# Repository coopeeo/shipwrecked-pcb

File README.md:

# shipwrecked-pcb
Shipwrecked PCB Badges

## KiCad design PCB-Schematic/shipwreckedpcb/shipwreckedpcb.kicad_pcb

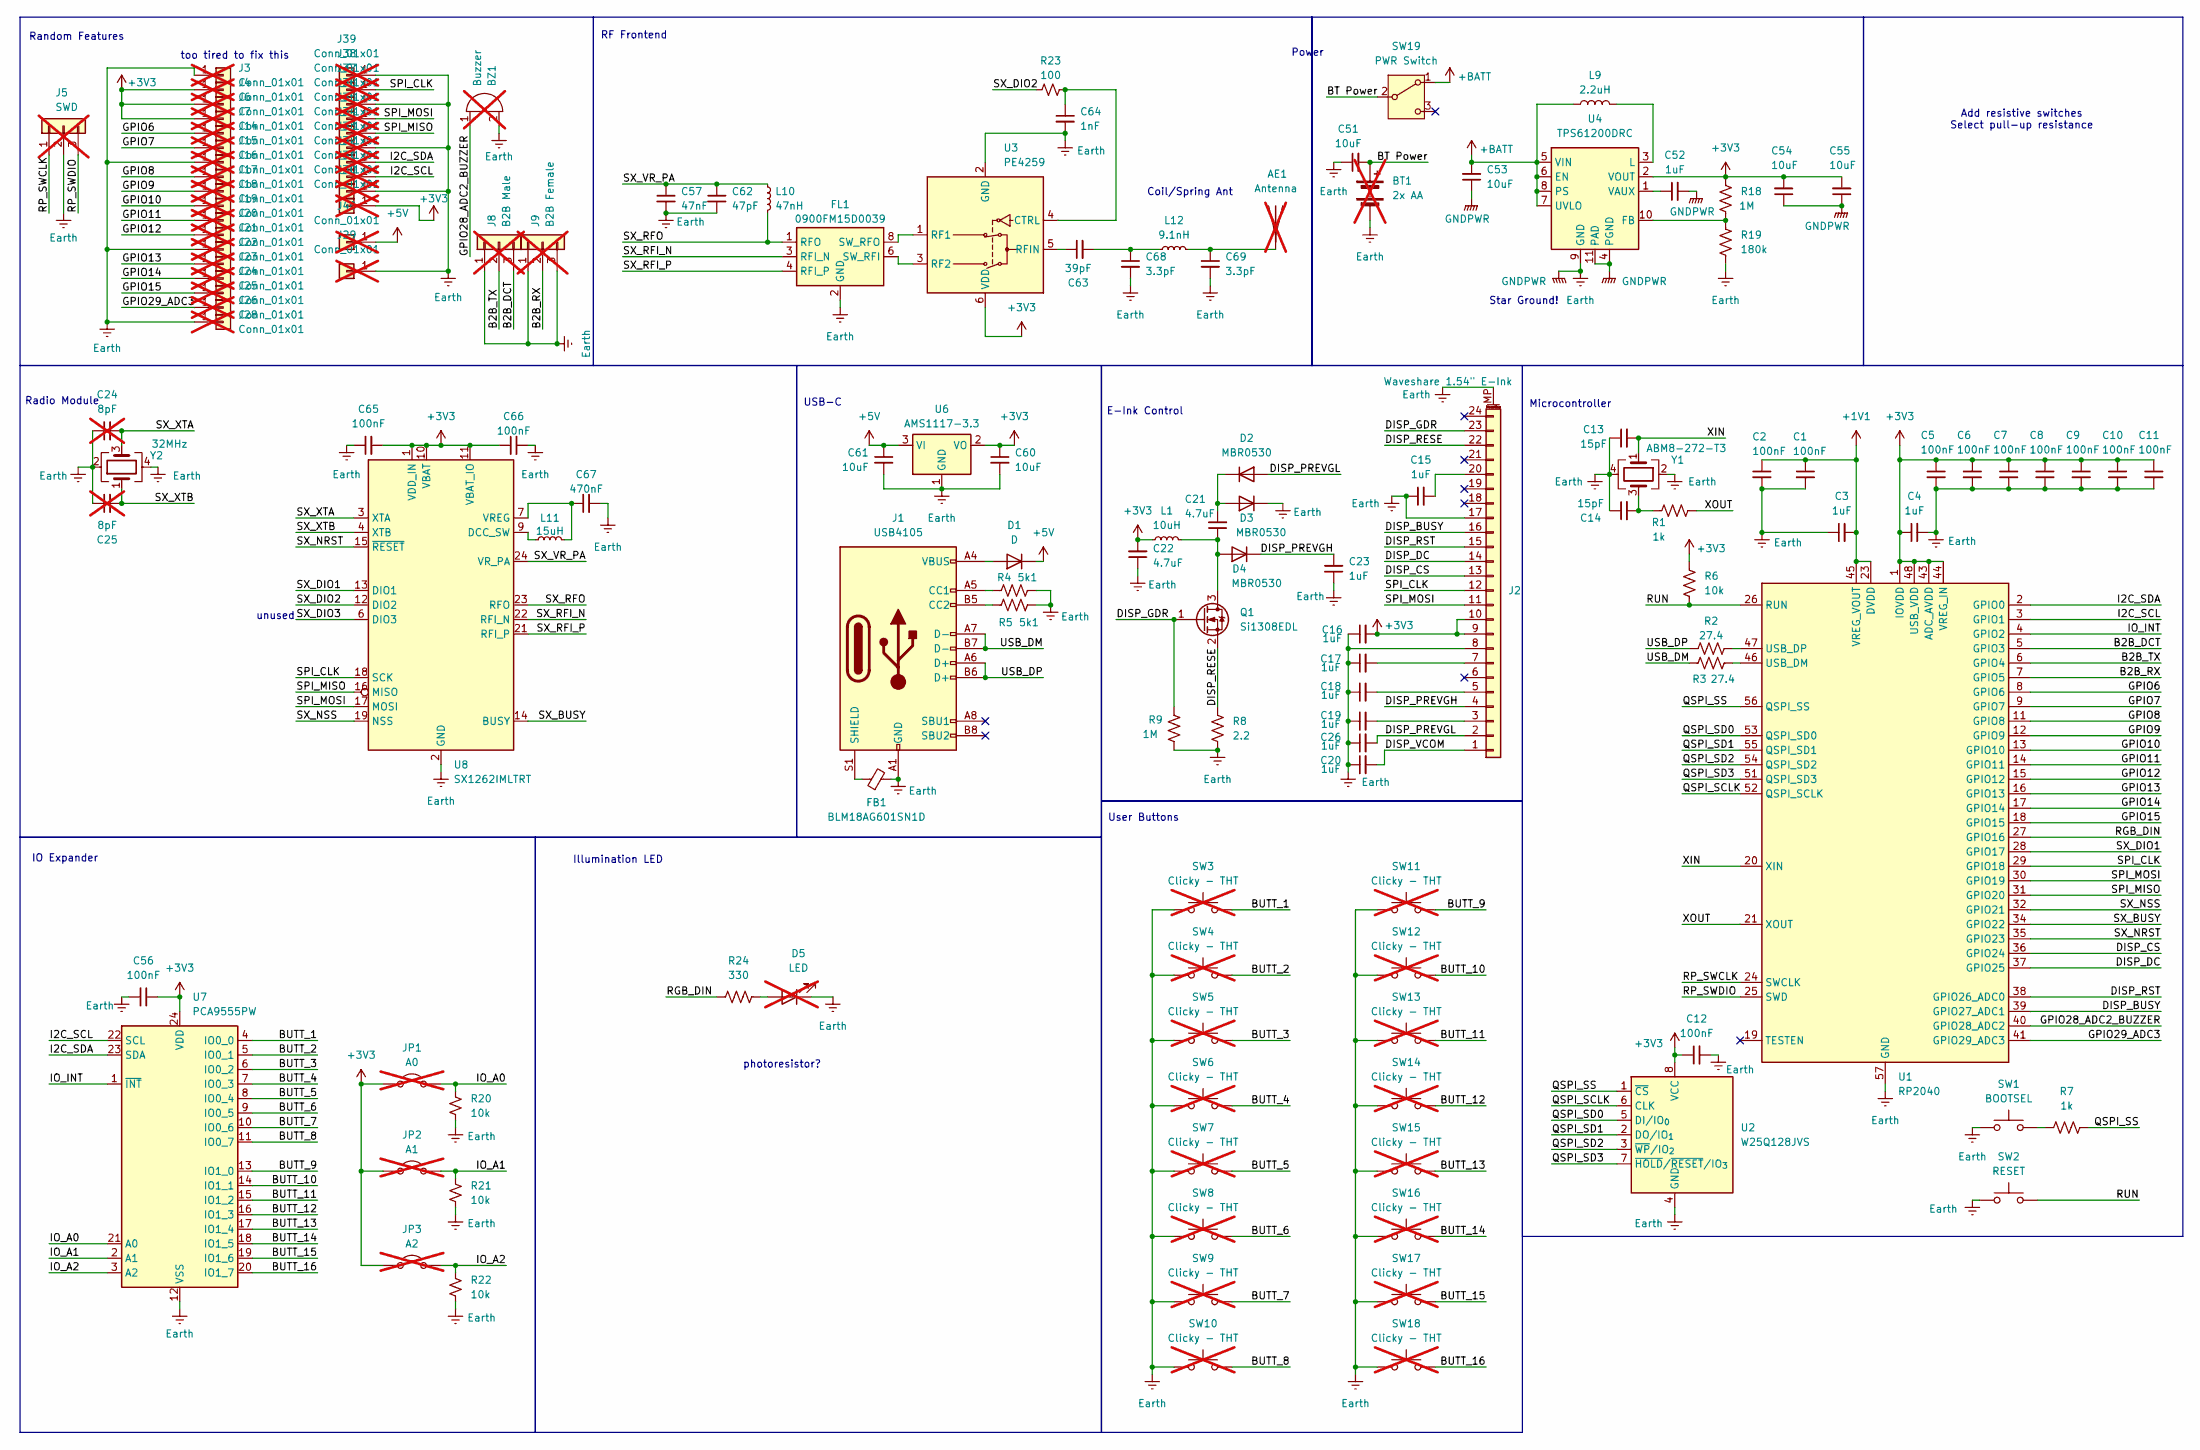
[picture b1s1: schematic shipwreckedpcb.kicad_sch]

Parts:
AE1: Antenna; PinSocket_1x01_P2.54mm_Vertical; not fitted
BT1: 2x AA; BatteryHolder_Keystone_2462_2xAA; not fitted
BZ1: Buzzer; Buzzer_D14mm_H7mm_P10mm; not fitted
C1, C2, C5, C6, C7, C8, C9, C10, C11, C12, C56, C65, C66: 100nF; C_0603_1608Metric; MPN CC0603KRX7R9BB104; LCSC Part C14663
C3, C4, C15, C16, C17, C18, C19, C20, C23, C26, C52: 1uF; C_0603_1608Metric; MPN CL10A105KB8NNNC; LCSC Part C15849
C13, C14: 15pF; C_0603_1608Metric; MPN CC0603JRNPO9BN150; LCSC Part C1644
C21, C22: 4.7uF; C_0603_1608Metric; MPN CL10A475KA8NQNC; LCSC Part C69335
C24, C25: 8pF; C_0603_1608Metric; MPN CC0603CRNPO9BN8R0; not fitted
C51, C53, C54, C55, C60, C61: 10uF; C_0603_1608Metric; MPN CL10A106KP8NNNC; LCSC Part C96446
C57: 47nF; C_0603_1608Metric; MPN CC0603KRX7R9BB473; LCSC Part C1622
C62: 47pF; C_0603_1608Metric; MPN CC0603JRNPO9BN470; LCSC Part C1671
C63: 39pF; C_0603_1608Metric; MPN CC0603JRNPO9BN101; LCSC Part C1666
C64: 1nF; C_0603_1608Metric; MPN CC0603KRX7R9BB102; LCSC Part C1588
C67: 470nF; C_0603_1608Metric; MPN CL10B474KA8NNNC; LCSC Part C1623
C68, C69: 3.3pF; C_0603_1608Metric; MPN 0603CG3R3C500NT; LCSC Part C1660
D1: D; D_SOD-123F; MPN 1N4001; LCSC Part C2892326
D2, D3, D4: MBR0530; D_SOD-123; MPN MBR0530T1G; LCSC Part C77336
D5: LED; LED_D5.0mm; MPN DY-324SVRC-H23-P-A4(FH); not fitted
FB1: BLM18AG601SN1D; R_0603_1608Metric; MPN BLM18AG601SN1D; LCSC Part C19330
FL1: 0900FM15D0039; Balun_Johanson_0900FM15K0039; MPN 0900FM15K0039E; LCSC Part consigned
J1: USB4105; USB_C_Receptacle_GCT_USB4105-xx-A_16P_TopMnt_Horizontal; MPN USB4105-GF-A; LCSC Part C3020560
J2: Waveshare 1.54" E-Ink; TE_2-1734839-4_1x24-1MP_P0.5mm_Horizontal; MPN 05B20U24P; LCSC Part C5362165
J3, J4, J6, J7, J14, J15, J16, J17, J18, J19, J20, J21, J22, J23, J24, J25, J26, J28, J29, J30, J31, J32, J33, J34, J35, J36, J37, J38, J39, J40: Conn_01x01; SolderWirePad_1x01_SMD_1x2mm; not fitted
J5: SWD; PinSocket_1x03_P2.54mm_Vertical; not fitted
J8: B2B Male; PinHeader_1x03_P2.54mm_Horizontal; not fitted
J9: B2B Female; PinSocket_1x03_P2.54mm_Horizontal; not fitted
JP1: A0; SolderJumper-2_P1.3mm_Open_RoundedPad1.0x1.5mm; not fitted
JP2: A1; SolderJumper-2_P1.3mm_Open_RoundedPad1.0x1.5mm; not fitted
JP3: A2; SolderJumper-2_P1.3mm_Open_RoundedPad1.0x1.5mm; not fitted
L1: 10uH; L_APV_ANR4018; MPN FNR4018S100MT; LCSC Part C167808
L9: 2.2uH; L_Taiyo-Yuden_NR-30xx; MPN NR3015T2R2M; LCSC Part C6364793
L10: 47nH; L_0603_1608Metric; MPN LS0603-47NJ-N; LCSC Part C285885
L11: 15uH; L_0805_2012Metric; MPN MLZ2012M150WT000; LCSC Part C383402
L12: 9.1nH; L_0603_1608Metric; MPN LS0603-47NJ-N; LCSC Part C334262
Q1: Si1308EDL; SOT-323_SC-70; MPN SI1308EDL; LCSC Part C7603347
R1, R7: 1k; R_0603_1608Metric; MPN RC0603FR-071KL; LCSC Part C21190
R2, R3: 27.4; R_0603_1608Metric; MPN FRC0603F27R4TS; LCSC Part C22926
R4, R5: 5k1; R_0603_1608Metric; MPN FRC0603F5101TS; LCSC Part C23186
R6, R20, R21, R22: 10k; R_0603_1608Metric; MPN RC0603FR-0710KL; LCSC Part C25804
R8: 2.2; R_0603_1608Metric; MPN CRCW06033R00FKEA; LCSC Part C22939
R9, R18: 1M; R_0603_1608Metric; MPN RC0603FR-071ML; LCSC Part C22935
R19: 180k; R_0603_1608Metric; MPN FRC0603F1803TS; LCSC Part C22827
R23: 100; R_0603_1608Metric; MPN RC0603FR-07100RL; LCSC Part C22775
R24: 330; R_0603_1608Metric; MPN RC0603FR-07330RL; LCSC Part C23138
SW1: BOOTSEL; SW_Tactile_SPST_NO_Straight_CK_PTS636Sx25SMTRLFS; MPN TS-1101-C-W; LCSC Part C318938
SW2: RESET; SW_Tactile_SPST_NO_Straight_CK_PTS636Sx25SMTRLFS; MPN TS-1101-C-W; LCSC Part C318938
SW3, SW4, SW5, SW6, SW7, SW8, SW9, SW10, SW11, SW12, SW13, SW14, SW15, SW16, SW17, SW18: Clicky - THT; SW_PUSH_6mm; MPN SH-6X6X4.3H-CJ; not fitted
SW19: PWR Switch; SW_SPDT_PCM12; MPN SK-3296S-01-L1; LCSC Part C319020
U1: RP2040; QFN-56-1EP_7x7mm_P0.4mm_EP3.2x3.2mm; MPN RP2040; LCSC Part C2040
U2: W25Q128JVS; SOIC-8_5.3x5.3mm_P1.27mm; MPN W25Q128JVSIQ; LCSC Part C97521
U3: PE4259; SOT-363_SC-70-6; MPN PE4259-63; LCSC Part C470892
U4: TPS61200DRC; Texas_S-PVSON-N10_ThermalVias; MPN TPS61200DRCR; LCSC Part C140320
U6: AMS1117-3.3; SOT-223-3_TabPin2; MPN AMS1117-3.3V; LCSC Part C18906017
U7: PCA9555PW; TSSOP-24_4.4x7.8mm_P0.65mm; MPN PCA9555PW,118; LCSC Part C128392
U8: SX1262IMLTRT; QFN-24-1EP_4x4mm_P0.5mm_EP2.6x2.6mm; MPN SX1262IMLTRT; LCSC Part C191341
Y1: ABM8-272-T3; Crystal_SMD_Abracon_ABM8G-4Pin_3.2x2.5mm; MPN XL2EL89CMI-111YLC-12M; LCSC Part C9002
Y2: 32MHz; Crystal_SMD_3225-4Pin_3.2x2.5mm; MPN XTM32032000DT00351001; LCSC Part C19723365

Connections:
+1V1: C1.1, C2.1, C3.2, U1.23 (DVDD), U1.45 (VREG_VOUT), U1.50 (DVDD)
+3V3: C4.1, C5.1, C6.1, C7.1, C8.1, C9.1, C10.1, C11.1, C12.1, C16.2, C22.2, C54.2, C55.2, C56.1, C60.1, C65.2, C66.1, J2.9, J2.10, J4.1, J6.1, J7.1, J30.1, JP1.1 (A), JP2.1 (A), JP3.1 (A), L1.1, R6.1, R18.1, U1.1 (IOVDD), U1.10 (IOVDD), U1.22 (IOVDD), U1.33 (IOVDD), U1.42 (IOVDD), U1.43 (ADC_AVDD), U1.44 (VREG_IN), U1.48 (USB_VDD), U1.49 (IOVDD), U2.8 (VCC), U3.6 (VDD), U4.2 (VOUT), U6.2 (VO), U7.24 (VDD), U8.1 (VDD_IN), U8.10 (VBAT), U8.11 (VBAT_IO)
+5V: C61.1, D1.1 (K), J40.1, U6.3 (VI)
+BATT: C53.2, L9.1, SW19.1 (A), U4.5 (VIN), U4.6 (EN), U4.7 (UVLO), U4.8 (PS)
/B2B_DCT: J8.3, U1.5 (GPIO3)
/B2B_RX: J9.2, U1.7 (GPIO5)
/B2B_TX: J8.2, U1.6 (GPIO4)
/BT Power: BT1.1 (+), C51.2, SW19.2 (B)
/BUTT_1: SW3.2, U7.4 (IO0_0)
/BUTT_2: SW4.2, U7.5 (IO0_1)
/BUTT_3: SW5.2, U7.6 (IO0_2)
/BUTT_4: SW6.2, U7.7 (IO0_3)
/BUTT_5: SW7.2, U7.8 (IO0_4)
/BUTT_6: SW8.2, U7.9 (IO0_5)
/BUTT_7: SW9.2, U7.10 (IO0_6)
/BUTT_8: SW10.2, U7.11 (IO0_7)
/BUTT_9: SW11.2, U7.13 (IO1_0)
/BUTT_10: SW12.2, U7.14 (IO1_1)
/BUTT_11: SW13.2, U7.15 (IO1_2)
/BUTT_12: SW14.2, U7.16 (IO1_3)
/BUTT_13: SW15.2, U7.17 (IO1_4)
/BUTT_14: SW16.2, U7.18 (IO1_5)
/BUTT_15: SW17.2, U7.19 (IO1_6)
/BUTT_16: SW18.2, U7.20 (IO1_7)
/DISP_BUSY: J2.16, U1.39 (GPIO27_ADC1)
/DISP_CS: J2.13, U1.36 (GPIO24)
/DISP_DC: J2.14, U1.37 (GPIO25)
/DISP_GDR: J2.23, Q1.1 (G), R9.1
/DISP_PREVGH: C23.2, D4.1 (K), J2.4
/DISP_PREVGL: C26.2, D2.2 (A), J2.2
/DISP_RESE: J2.22, Q1.2 (S), R8.1
/DISP_RST: J2.15, U1.38 (GPIO26_ADC0)
/DISP_VCOM: C20.2, J2.1
/GPIO6: J14.1, U1.8 (GPIO6)
/GPIO7: J15.1, U1.9 (GPIO7)
/GPIO8: J17.1, U1.11 (GPIO8)
/GPIO9: J18.1, U1.12 (GPIO9)
/GPIO10: J19.1, U1.13 (GPIO10)
/GPIO11: J20.1, U1.14 (GPIO11)
/GPIO12: J21.1, U1.15 (GPIO12)
/GPIO13: J23.1, U1.16 (GPIO13)
/GPIO14: J24.1, U1.17 (GPIO14)
/GPIO15: J25.1, U1.18 (GPIO15)
/GPIO28_ADC2_BUZZER: BZ1.1 (+), U1.40 (GPIO28_ADC2)
/GPIO29_ADC3: J26.1, U1.41 (GPIO29_ADC3)
/I2C_SCL: J32.1, U1.3 (GPIO1), U7.22 (SCL)
/I2C_SDA: J33.1, U1.2 (GPIO0), U7.23 (SDA)
/IO_A0: JP1.2 (B), R20.1, U7.21 (A0)
/IO_A1: JP2.2 (B), R21.1, U7.2 (A1)
/IO_A2: JP3.2 (B), R22.1, U7.3 (A2)
/IO_INT: U1.4 (GPIO2), U7.1 (~INT)
/QSPI_SCLK: U1.52 (QSPI_SCLK), U2.6 (CLK)
/QSPI_SD0: U1.53 (QSPI_SD0), U2.5 (DI/IO_{0})
/QSPI_SD1: U1.55 (QSPI_SD1), U2.2 (DO/IO_{1})
/QSPI_SD2: U1.54 (QSPI_SD2), U2.3 (~WP/IO_{2})
/QSPI_SD3: U1.51 (QSPI_SD3), U2.7 (~HOLD/~RESET/IO_{3})
/QSPI_SS: R7.2, U1.56 (QSPI_SS), U2.1 (~CS)
/RGB_DIN: R24.1, U1.27 (GPIO16)
/RP_SWCLK: J5.1, U1.24 (SWCLK)
/RP_SWDIO: J5.3, U1.25 (SWD)
/RUN: R6.2, SW2.2, U1.26 (RUN)
/SPI_CLK: J2.12, J38.1, U1.29 (GPIO18), U8.18 (SCK)
/SPI_MISO: J35.1, U1.31 (GPIO20), U8.16 (MISO)
/SPI_MOSI: J2.11, J36.1, U1.30 (GPIO19), U8.17 (MOSI)
/SX_BUSY: U1.34 (GPIO22), U8.14 (BUSY)
/SX_DIO1: U1.28 (GPIO17), U8.13 (DIO1)
/SX_DIO2: R23.1, U8.12 (DIO2)
/SX_DIO3: U8.6 (DIO3)
/SX_NRST: U1.35 (GPIO23), U8.15 (~RESET)
/SX_NSS: U1.32 (GPIO21), U8.19 (NSS)
/SX_RFI_N: FL1.3 (RFI_N), U8.22 (RFI_N)
/SX_RFI_P: FL1.4 (RFI_P), U8.21 (RFI_P)
/SX_RFO: FL1.1 (RFO), L10.2, U8.23 (RFO)
/SX_VR_PA: C57.1, C62.1, L10.1, U8.24 (VR_PA)
/SX_XTA: C24.2, U8.3 (XTA), Y2.3
/SX_XTB: C25.2, U8.4 (XTB), Y2.1
/USB_DM: J1.A7 (D-), J1.B7 (D-), R3.1
/USB_DP: J1.A6 (D+), J1.B6 (D+), R2.1
/XIN: C13.2, U1.20 (XIN), Y1.1
/XOUT: R1.2, U1.21 (XOUT)
Earth: BT1.2 (-), BZ1.2 (-), C1.2, C2.2, C3.1, C4.2, C5.2, C6.2, C7.2, C8.2, C9.2, C10.2, C11.2, C12.2, C13.1, C14.1, C15.1, C16.1, C17.1, C18.1, C19.1, C20.1, C22.1, C23.1, C24.1, C25.1, C26.1, C51.1, C52.2, C53.1, C54.1, C55.1, C56.2, C57.2, C60.2, C61.2, C62.2, C64.2, C65.1, C66.2, C67.2, C68.2, C69.2, D3.1 (K), D5.1 (K), FB1.2, FL1.2 (GND), FL1.5 (GND), FL1.7 (GND), FL1.9 (GND), FL1.10 (GND), J1.A1 (GND), J1.A12 (GND), J1.B1 (GND), J1.B12 (GND), J2.8, J2.17, J2.MP (MountPin), J3.1, J5.2, J8.1, J9.1, J9.3, J16.1, J22.1, J28.1, J29.1, J31.1, J34.1, J37.1, J39.1, R4.2, R5.2, R8.2, R9.2, R19.2, R20.2, R21.2, R22.2, SW1.1, SW2.1, SW3.1, SW4.1, SW5.1, SW6.1, SW7.1, SW8.1, SW9.1, SW10.1, SW11.1, SW12.1, SW13.1, SW14.1, SW15.1, SW16.1, SW17.1, SW18.1, U1.57 (GND), U2.4 (GND), U3.2 (GND), U4.4 (PGND), U4.9 (GND), U4.11 (PAD), U6.1 (GND), U7.12 (VSS), U8.2 (GND), U8.5 (GND), U8.8 (GND), U8.20 (GND), U8.25 (GND), Y1.2, Y1.4, Y2.2, Y2.4
unnamed: AE1.1 (A), C69.1, L12.2
unnamed: C14.2, R1.1, Y1.3
unnamed: C63.2, C68.1, L12.1
unnamed: D1.2 (A), J1.A4 (VBUS), J1.A9 (VBUS), J1.B4 (VBUS), J1.B9 (VBUS)
unnamed: C21.2, D2.1 (K), D3.2 (A)
unnamed: C21.1, D4.2 (A), L1.2, Q1.3 (D)
unnamed: D5.2 (A), R24.2
unnamed: FL1.6 (SW_RFI), U3.3 (RF2)
unnamed: FL1.8 (SW_RFO), U3.1 (RF1)
unnamed: J1.A5 (CC1), R4.1
unnamed: J1.B5 (CC2), R5.1
unnamed: FB1.1, J1.S1 (SHIELD)
unnamed: C19.2, J2.3
unnamed: C18.2, J2.5
unnamed: C17.2, J2.7
unnamed: C15.2, J2.20
unnamed: R7.1, SW1.2
unnamed: R3.2, U1.46 (USB_DM)
unnamed: R2.2, U1.47 (USB_DP)
unnamed: C64.1, R23.2, U3.4 (CTRL)
unnamed: C63.1, U3.5 (RFIN)
unnamed: R18.2, R19.1, U4.10 (FB)
unnamed: L9.2, U4.3 (L)
unnamed: C52.1, U4.1 (VAUX)
unnamed: L11.1, U8.9 (DCC_SW)
unnamed: C67.1, L11.2, U8.7 (VREG)

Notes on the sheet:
IO Expander
photoresistor?
Illumination LED
Power
Add resistive switches Select pull-up resistance
Microcontroller
E-Ink Control
unused
User Buttons
Star Ground!
too tired to fix this
Coil/Spring Ant
Random Features
RF Frontend
USB-C
Radio Module

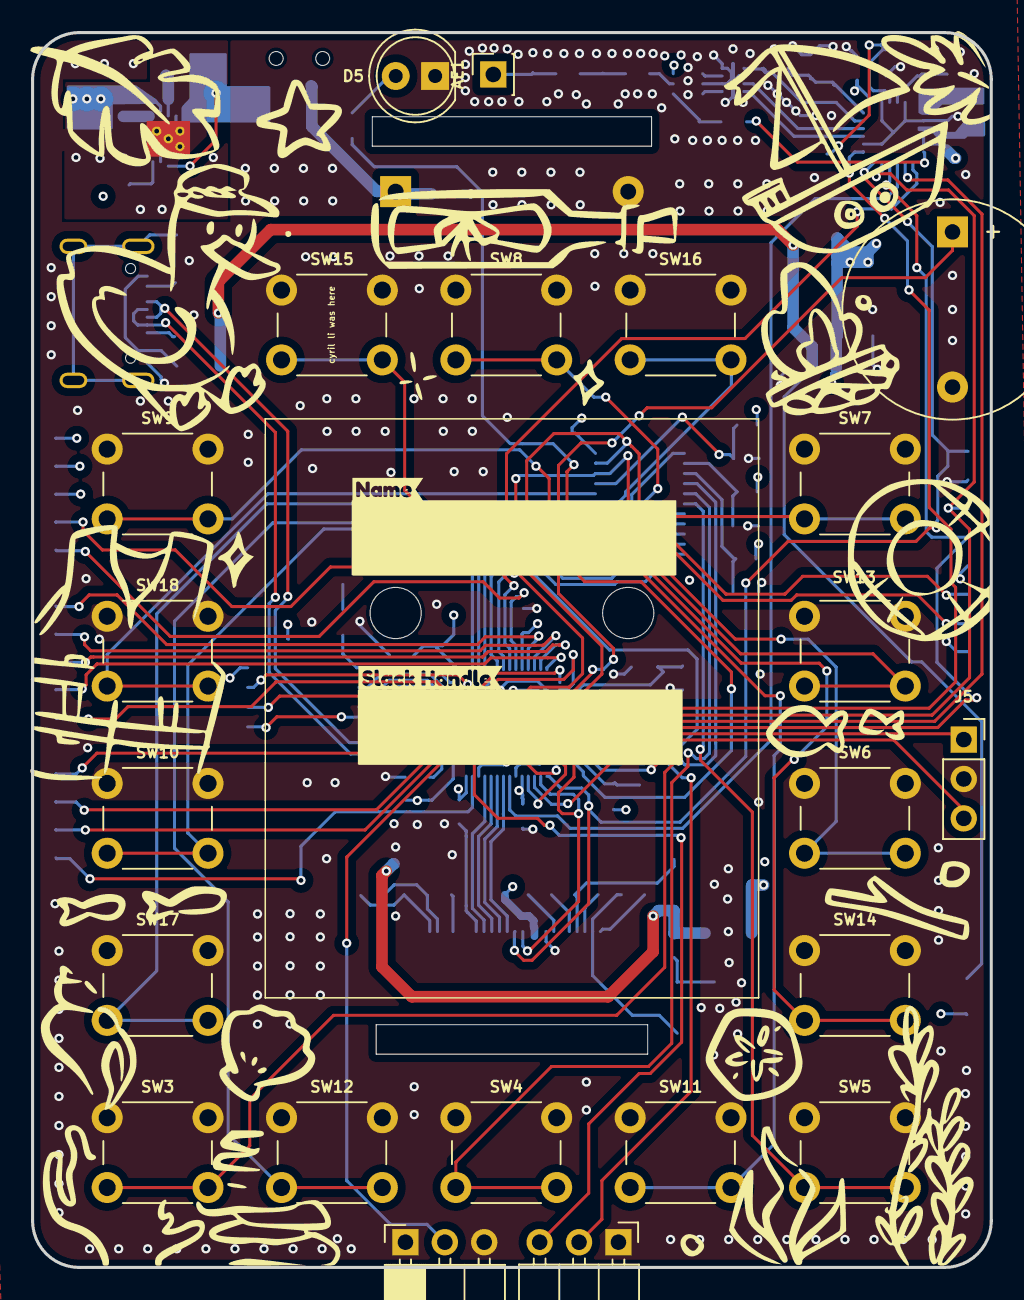
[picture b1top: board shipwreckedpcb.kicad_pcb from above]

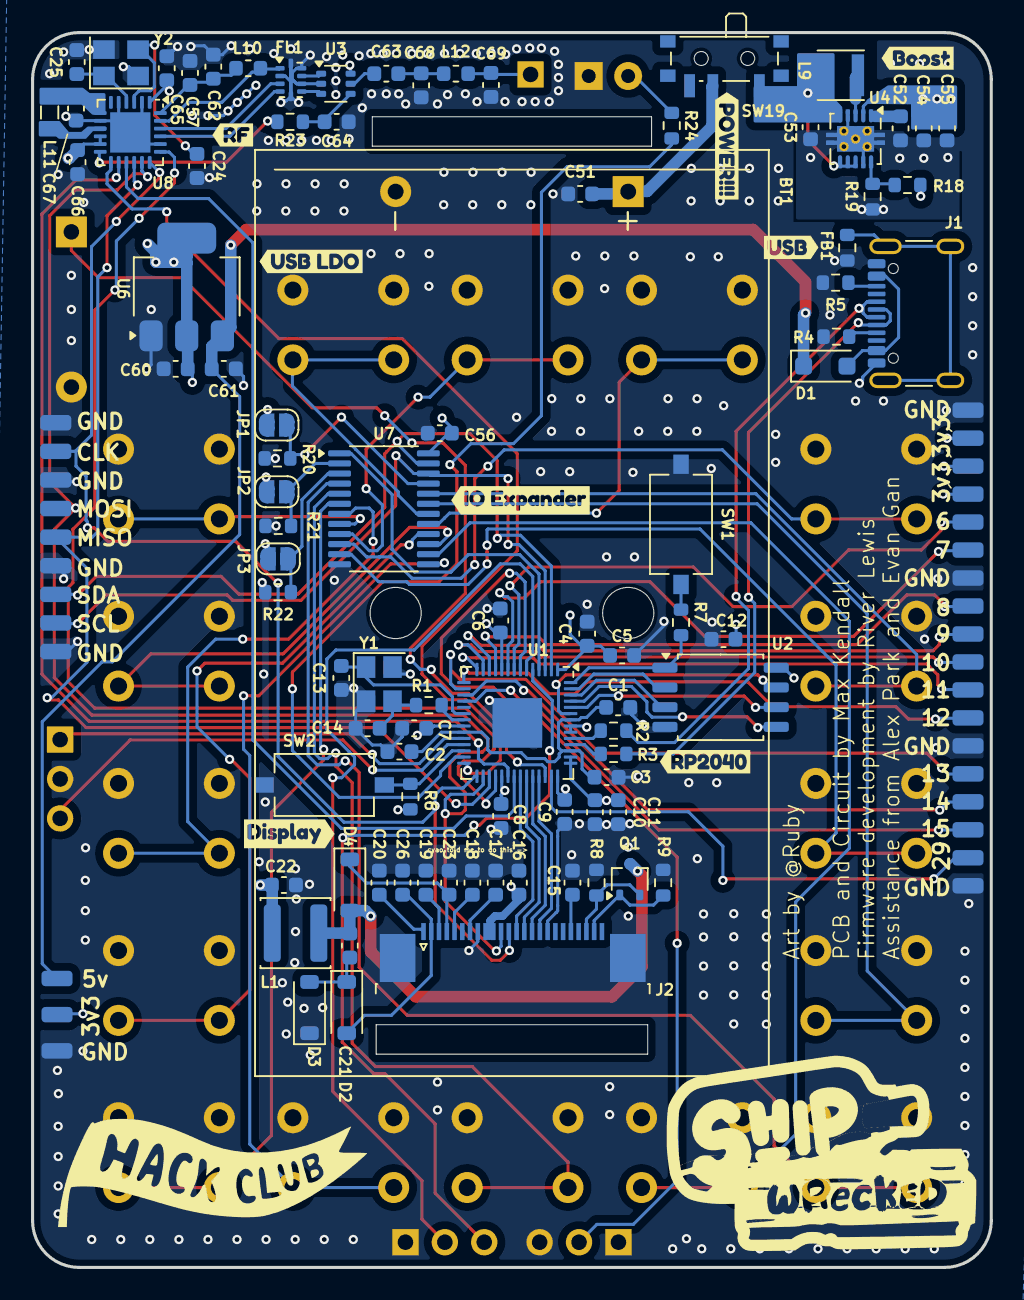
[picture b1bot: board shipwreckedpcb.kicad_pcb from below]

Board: 4 copper layers, 61.8 x 79.6 mm, 151 parts (127 on the bottom side), 106 nets.

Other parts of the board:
kibuzzard-687A9D67: G***; kibuzzard-687A9D67
kibuzzard-687A9DB2: G***; kibuzzard-687A9DB2
kibuzzard-687ADB8B: G***; kibuzzard-687ADB8B
kibuzzard-687864C4: G***; kibuzzard-687864C4
kibuzzard-687865CB: G***; kibuzzard-687865CB
kibuzzard-6878653F: G***; kibuzzard-6878653F
kibuzzard-6878659A: G***; kibuzzard-6878659A
kibuzzard-68786508: G***; kibuzzard-68786508
kibuzzard-68786528: G***; kibuzzard-68786528
kibuzzard-68786588: G***; kibuzzard-68786588

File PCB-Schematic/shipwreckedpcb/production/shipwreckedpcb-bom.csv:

Reference,Qty,Comment,Footprint,LCSC Part
"C1,C2,C5,C6,C7,C8,C9,C10,C11,C12,C56,C65,C66",13,100nF,Capacitor_SMD:C_0603_1608Metric,C14663
"C3,C4,C15,C16,C17,C18,C19,C20,C23,C26,C52",11,1uF 25v,Capacitor_SMD:C_0603_1608Metric,C15849
"C13,C14",2,15pF,Capacitor_SMD:C_0603_1608Metric,C1644
"C21,C22",2,4.7uF 25v,Capacitor_SMD:C_0603_1608Metric,C69335
"C51,C53,C54,C55,C60,C61",6,10uF,Capacitor_SMD:C_0603_1608Metric,C96446
C57,1,47nF,Capacitor_SMD:C_0603_1608Metric,C1622
C62,1,47pF,Capacitor_SMD:C_0603_1608Metric,C1671
C63,1,39pF,Capacitor_SMD:C_0603_1608Metric,C1666
C64,1,1nF,Capacitor_SMD:C_0603_1608Metric,C1588
C67,1,470nF,Capacitor_SMD:C_0603_1608Metric,C1623
"C68,C69",2,3.3pF,Capacitor_SMD:C_0603_1608Metric,C1660
D1,1,D,Diode_SMD:D_SOD-123F,C2892326
"D2,D3,D4",3,MBR0530,Diode_SMD:D_SOD-123,C77336
FB1,1,BLM18AG601SN1D,Resistor_SMD:R_0603_1608Metric,C19330
FL1,1,0900FM15D0039 - CONSIGNED,RF_Converter:Balun_Johanson_0900FM15K0039,C1513363
J1,1,USB4105,Connector_USB:USB_C_Receptacle_GCT_USB4105-xx-A_16P_TopMnt_Horizontal,C3020560
J2,1,"Waveshare 1.54"" E-Ink",Connector_FFC-FPC:TE_2-1734839-4_1x24-1MP_P0.5mm_Horizontal,C5362165
L1,1,10uH,Inductor_SMD:L_APV_ANR4018,C167808
L9,1,2.2uH,Inductor_SMD:L_Taiyo-Yuden_NR-30xx,C6364793
L10,1,47nH,Inductor_SMD:L_0603_1608Metric,C285885
L11,1,15uH,Inductor_SMD:L_0805_2012Metric,C383402
L12,1,9.1nH,Inductor_SMD:L_0603_1608Metric,C77125
Q1,1,Si1308EDL,Package_TO_SOT_SMD:SOT-323_SC-70,C7603347
"R1,R7",2,1k,Resistor_SMD:R_0603_1608Metric,C21190
"R2,R3",2,27.4,Resistor_SMD:R_0603_1608Metric,C22926
"R4,R5",2,5k1,Resistor_SMD:R_0603_1608Metric,C23186
"R6,R20,R21,R22",4,10k,Resistor_SMD:R_0603_1608Metric,C25804
R8,1,2.2,Resistor_SMD:R_0603_1608Metric,C22939
"R9,R18",2,1M,Resistor_SMD:R_0603_1608Metric,C22935
R19,1,180k,Resistor_SMD:R_0603_1608Metric,C22827
R23,1,100,Resistor_SMD:R_0603_1608Metric,C22775
R24,1,330,Resistor_SMD:R_0603_1608Metric,C23138
SW1,1,BOOTSEL,Button_Switch_SMD:SW_Tactile_SPST_NO_Straight_CK_PTS636Sx25SMTRLFS,C318938
SW2,1,RESET,Button_Switch_SMD:SW_Tactile_SPST_NO_Straight_CK_PTS636Sx25SMTRLFS,C318938
SW19,1,PWR Switch,Button_Switch_SMD:SW_SPDT_PCM12,C319020
U1,1,RP2040,Package_DFN_QFN:QFN-56-1EP_7x7mm_P0.4mm_EP3.2x3.2mm,C2040
U2,1,W25Q128JVS,Package_SO:SOIC-8_5.3x5.3mm_P1.27mm,C97521
U3,1,PE4259,Package_TO_SOT_SMD:SOT-363_SC-70-6, C470892
U4,1,TPS61200DRC,Package_SON:Texas_S-PVSON-N10_ThermalVias,C140320
U6,1,AMS1117-3.3,Package_TO_SOT_SMD:SOT-223-3_TabPin2,C18906017
U7,1,PCA9555PW,Package_SO:TSSOP-24_4.4x7.8mm_P0.65mm,C128392
U8,1,SX1262IMLTRT,Package_DFN_QFN:QFN-24-1EP_4x4mm_P0.5mm_EP2.6x2.6mm,C191341
Y1,1,12MHz,Crystal:Crystal_SMD_Abracon_ABM8G-4Pin_3.2x2.5mm,C9002
Y2,1,32MHz,Crystal:Crystal_SMD_3225-4Pin_3.2x2.5mm,C19723365

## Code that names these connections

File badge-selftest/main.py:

# a self-test program for the badge
# tests:
# - display
# - buttons
# - buzzer
# - LED
# - radio

from machine import Pin, SPI, I2C, PWM, unique_id
import utime

spi = SPI(0, baudrate=1_000_000, polarity=0, phase=0, sck=Pin(18), mosi=Pin(19), miso=Pin(20))

print("--- Starting self-test---")
print("---- Testing LED ----")

led = PWM(Pin(16))
led.freq(5000)

led.duty_u16(10_000)  # Turn on LED
utime.sleep(1)  # Wait for 1 second
led.duty_u16(0)  # Turn off LED

print("---- Testing display ----")

from einkdriver import EPD
disp_cs = Pin(24, Pin.OUT)
disp_dc = Pin(25, Pin.OUT)
disp_rst = Pin(26, Pin.OUT)
disp_busy = Pin(27, Pin.IN)

print("Initializing E-Ink display...")
display = EPD(spi, disp_cs, disp_dc, disp_rst, disp_busy)
display.init()

print("Displaying base image...")
display.fill(1)  # Fill with white
display.text("badge self-test", 10, 10, 0)
display.text("Press any button on the badge", 10, 30, 0)
display.text(f"Badge ID: {unique_id().hex()[-4:]}", 10, 50, 0) 
display.display()
display.sleep()
utime.sleep(5)  # Allow time for display to update

print("---- Testing buttons ----")
ADDRESS: int = 0x20  # I2C address of PCA9555
INPUT_PORT_0: int = 0x00
INPUT_PORT_1: int = 0x01
CONFIG_PORT_0: int = 0x06
CONFIG_PORT_1: int = 0x07

i2c = I2C(0, scl=Pin(1), sda=Pin(0))

# initialize the PCA9555 I/O expander
i2c.writeto_mem(ADDRESS, CONFIG_PORT_0, bytearray([0xff])) # set the bottom 8 pins as inputs
i2c.writeto_mem(ADDRESS, CONFIG_PORT_1, bytearray([0xff])) # set the top 8 pins as inputs

button_pressed = None
print("Press a button on the badge to continue...")

while button_pressed is None:
    raw_data = i2c.readfrom_mem(ADDRESS, INPUT_PORT_0, 2)
    for i in range(16):
        # Check if the button is pressed (active low)
        if not (raw_data[i // 8] & (1 << (i % 8))):
            button_pressed = i
            print(f"Button {i} pressed!")
            break
    utime.sleep(0.1)  # Polling delay

display.text(f"Button {button_pressed} pressed!", 10, 70, 0)
display.display()
display.sleep()

print("---- Testing buzzer ----")
def tone(frequency, duration):
    buzzer.freq(frequency)
    buzzer.duty_u16(10_000)  # Set duty cycle to 100%
    utime.sleep(duration)
    buzzer.duty_u16(0)  # Turn off buzzer

buzzer = PWM(Pin(28))
# simple melody
tone(523, 0.5) # C5
utime.sleep(0.1)
tone(392, 0.25) # G4
utime.sleep(0.05)
tone(392, 0.25) # G4
utime.sleep(0.05)
tone(415, 0.5) # G#4
utime.sleep(0.7)
tone(493, 0.5) # B4
utime.sleep(0.1)
tone(523, 0.5) # C5

print("--- Test completed ---")

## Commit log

2025-05-21 add local files
2025-05-21 Backlink to CADLAB.io has been added.
2025-05-21 move files to correct folder
2025-05-21 hopefully preview works now?
2025-05-22 finished first version of schematic
2025-05-23 add footprints for everything (just gotta sort out the touch pads)
2025-05-23 finish assigning footprints, made resistive button
2025-05-25 add power to lights (oops), lay out individual sections, add rough placement
2025-05-25 finish placing components
2025-05-27 start routing
2025-05-27 production files (tentative)
2025-05-27 boost conv, leds, caps, added ldo for usb
2025-05-29 finished buttons, removed nfc, routed interface headers
2025-05-30 made some progress with the expansion headers
2025-05-31 finished all the gpio + buzzer
2025-06-24 fixed drc errors, added stitching vias
2025-06-26 started sx1262
2025-06-27 finished prototype?
2025-06-27 silkscreen + prod files
2025-06-27 add bom
2025-06-28 add initial implementation of app api
2025-06-28 add emulator
2025-06-30 start on a skeleton of the firmware
2025-07-01 implement some of the hardware libs (untested)
2025-07-02 start to implement app launch logic
2025-07-03 add some untested radio stuff
2025-07-03 add test script (which is untested)
2025-07-05 rename BadgeOS to InternalOS
2025-07-05 start implementing app-facing API
2025-07-05 add contacts db and iface
2025-07-15 fix dumb stuff
    turns out you need to:
    - give power :0
    - add vgl cap
    - not FLIP THE CONNECTOR :heavysob:
    - still need to do buttons
2025-07-15 first pass on clicky buttons
2025-07-18 that feeling when you do your homework on the bus
2025-07-18 avoiding alex's question (and shifting vias and fixing broken trace)
2025-07-18 crosstalk is a myth propagated by those in power
2025-07-18 yolo
2025-07-18 silkscreen updates
2025-07-18 if i didn't click update pcb from schematic i wouldn't have noticed i deleted the battery
2025-07-19 bom and buzzer
2025-07-19 3d models
2025-07-20 net lalbels neater
2025-07-20 orientations
2025-07-21 add production files
2025-07-22 THANK YOU CYRIL
2025-07-22 a via a day keeps the emi away
2025-07-22 and jlc numbers, fix silkscreen
2025-07-22 new prod files
2025-07-22 jlc-friendly files
2025-07-23 prod
2025-07-23 Implement most of the app-facing API
2025-07-23 oops didn't mean to touch files outside of ./Code/*
2025-07-25 test on real hardware and refine app launcher!
2025-07-25 app launcher work!
2025-07-30 Add nicer fonts and a badge app, and display errors on eink
2025-07-31 Create webflasher skeletion
2025-07-31 Create VERSION
2025-07-31 Change display pinout for testing
2025-07-31 fix minor bug in buttons.py (webflasher test)
2025-07-31 bump version (webflasher test)
2025-07-31 switch back to real badge pinout
2025-07-31 proof-of-concept web flasher/configurator!
2025-08-02 my git is very out of date :noo: fix self-test fix minor bugs in buttons + display fix 3d models in pcb
2025-08-03 good script
2025-08-03 full length led
2025-08-05 super duper wip of radio
2025-08-05 top-level radio api implemented + tested
2025-08-06 Add half-tested cryptographically signed announcements sending and receiving
2025-08-07 flesh out more of announcements, make packets not corrupt and dispatching works as well and this is a really long git commit message
2025-08-07 Respect config.json, display badge id in badge app, and try creating a GitHub action to build new releases
2025-08-07 add permission to action
2025-08-07 webflasher: App support, custom firmware and uploading from GH releases
2025-08-07 webflasher is feature-complete! now it just needs to be deployed
2025-08-07 try deploying to GH Pages
2025-08-07 don't fail the build on a warning
2025-08-07 use the firmware-zips branch as cdn-alike instead of releases
2025-08-07 add gitignore
2025-08-07 Add firmware v0.0.3
2025-08-07 fetch firmware from the correct location
2025-08-07 fix homepage so site builds properly
2025-08-07 dummy commit to kick actions into pulling a good homepage
2025-08-07 GOT YOU
2025-08-07 add some uart stuff + make home screen use 2 buttons
2025-08-07 remove unused functions and permissions and document much of the badge API
2025-08-08 add led, add notifications to announcements
2025-08-08 use proper button names and switch from PermissionError to RuntimeError
2025-08-08 launch home screen on startup and don't display home-screen in the home screen
2025-08-08 home screen on startup, feedback on button press
2025-08-08 fix wrapping on default badge text
2025-08-08 increase font size for badge app
2025-08-08 don't require logoPath to upload
2025-08-08 remove hello-world app
2025-08-08 bump version
2025-08-08 Add firmware v0.1.0
2025-08-08 text wrapping and default message fixes in announcements
2025-08-08 fix home screen nav issues
2025-08-08 some more progress on uart
2025-08-08 typo on home screen
2025-08-08 announcement sender: only try once (for now)
2025-08-08 workaround for OSError 84 (untested)
2025-08-08 fix announcement retries
2025-08-08 Version v1.0.0!
2025-08-08 Add firmware v1.0.0
2025-08-08 better wrapping logic in badge app
2025-08-08 Add firmware v1.1.0
2025-08-09 close to final version
2025-08-09 Revert "close to final version"
    This reverts commit 66ef5ae6c3deaef1d89c793caf92375dbea4f24f.
2025-08-09 correct a few things
    - correct page buttons on homescreen
    - add before close function working
    - add a little like light when SW15 is hit
